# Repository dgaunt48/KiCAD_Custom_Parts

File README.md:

# KiCad Custom Parts

Symbols, Footprints and 3dModels used in my schematics which are not part of the standard KiCad libraries.

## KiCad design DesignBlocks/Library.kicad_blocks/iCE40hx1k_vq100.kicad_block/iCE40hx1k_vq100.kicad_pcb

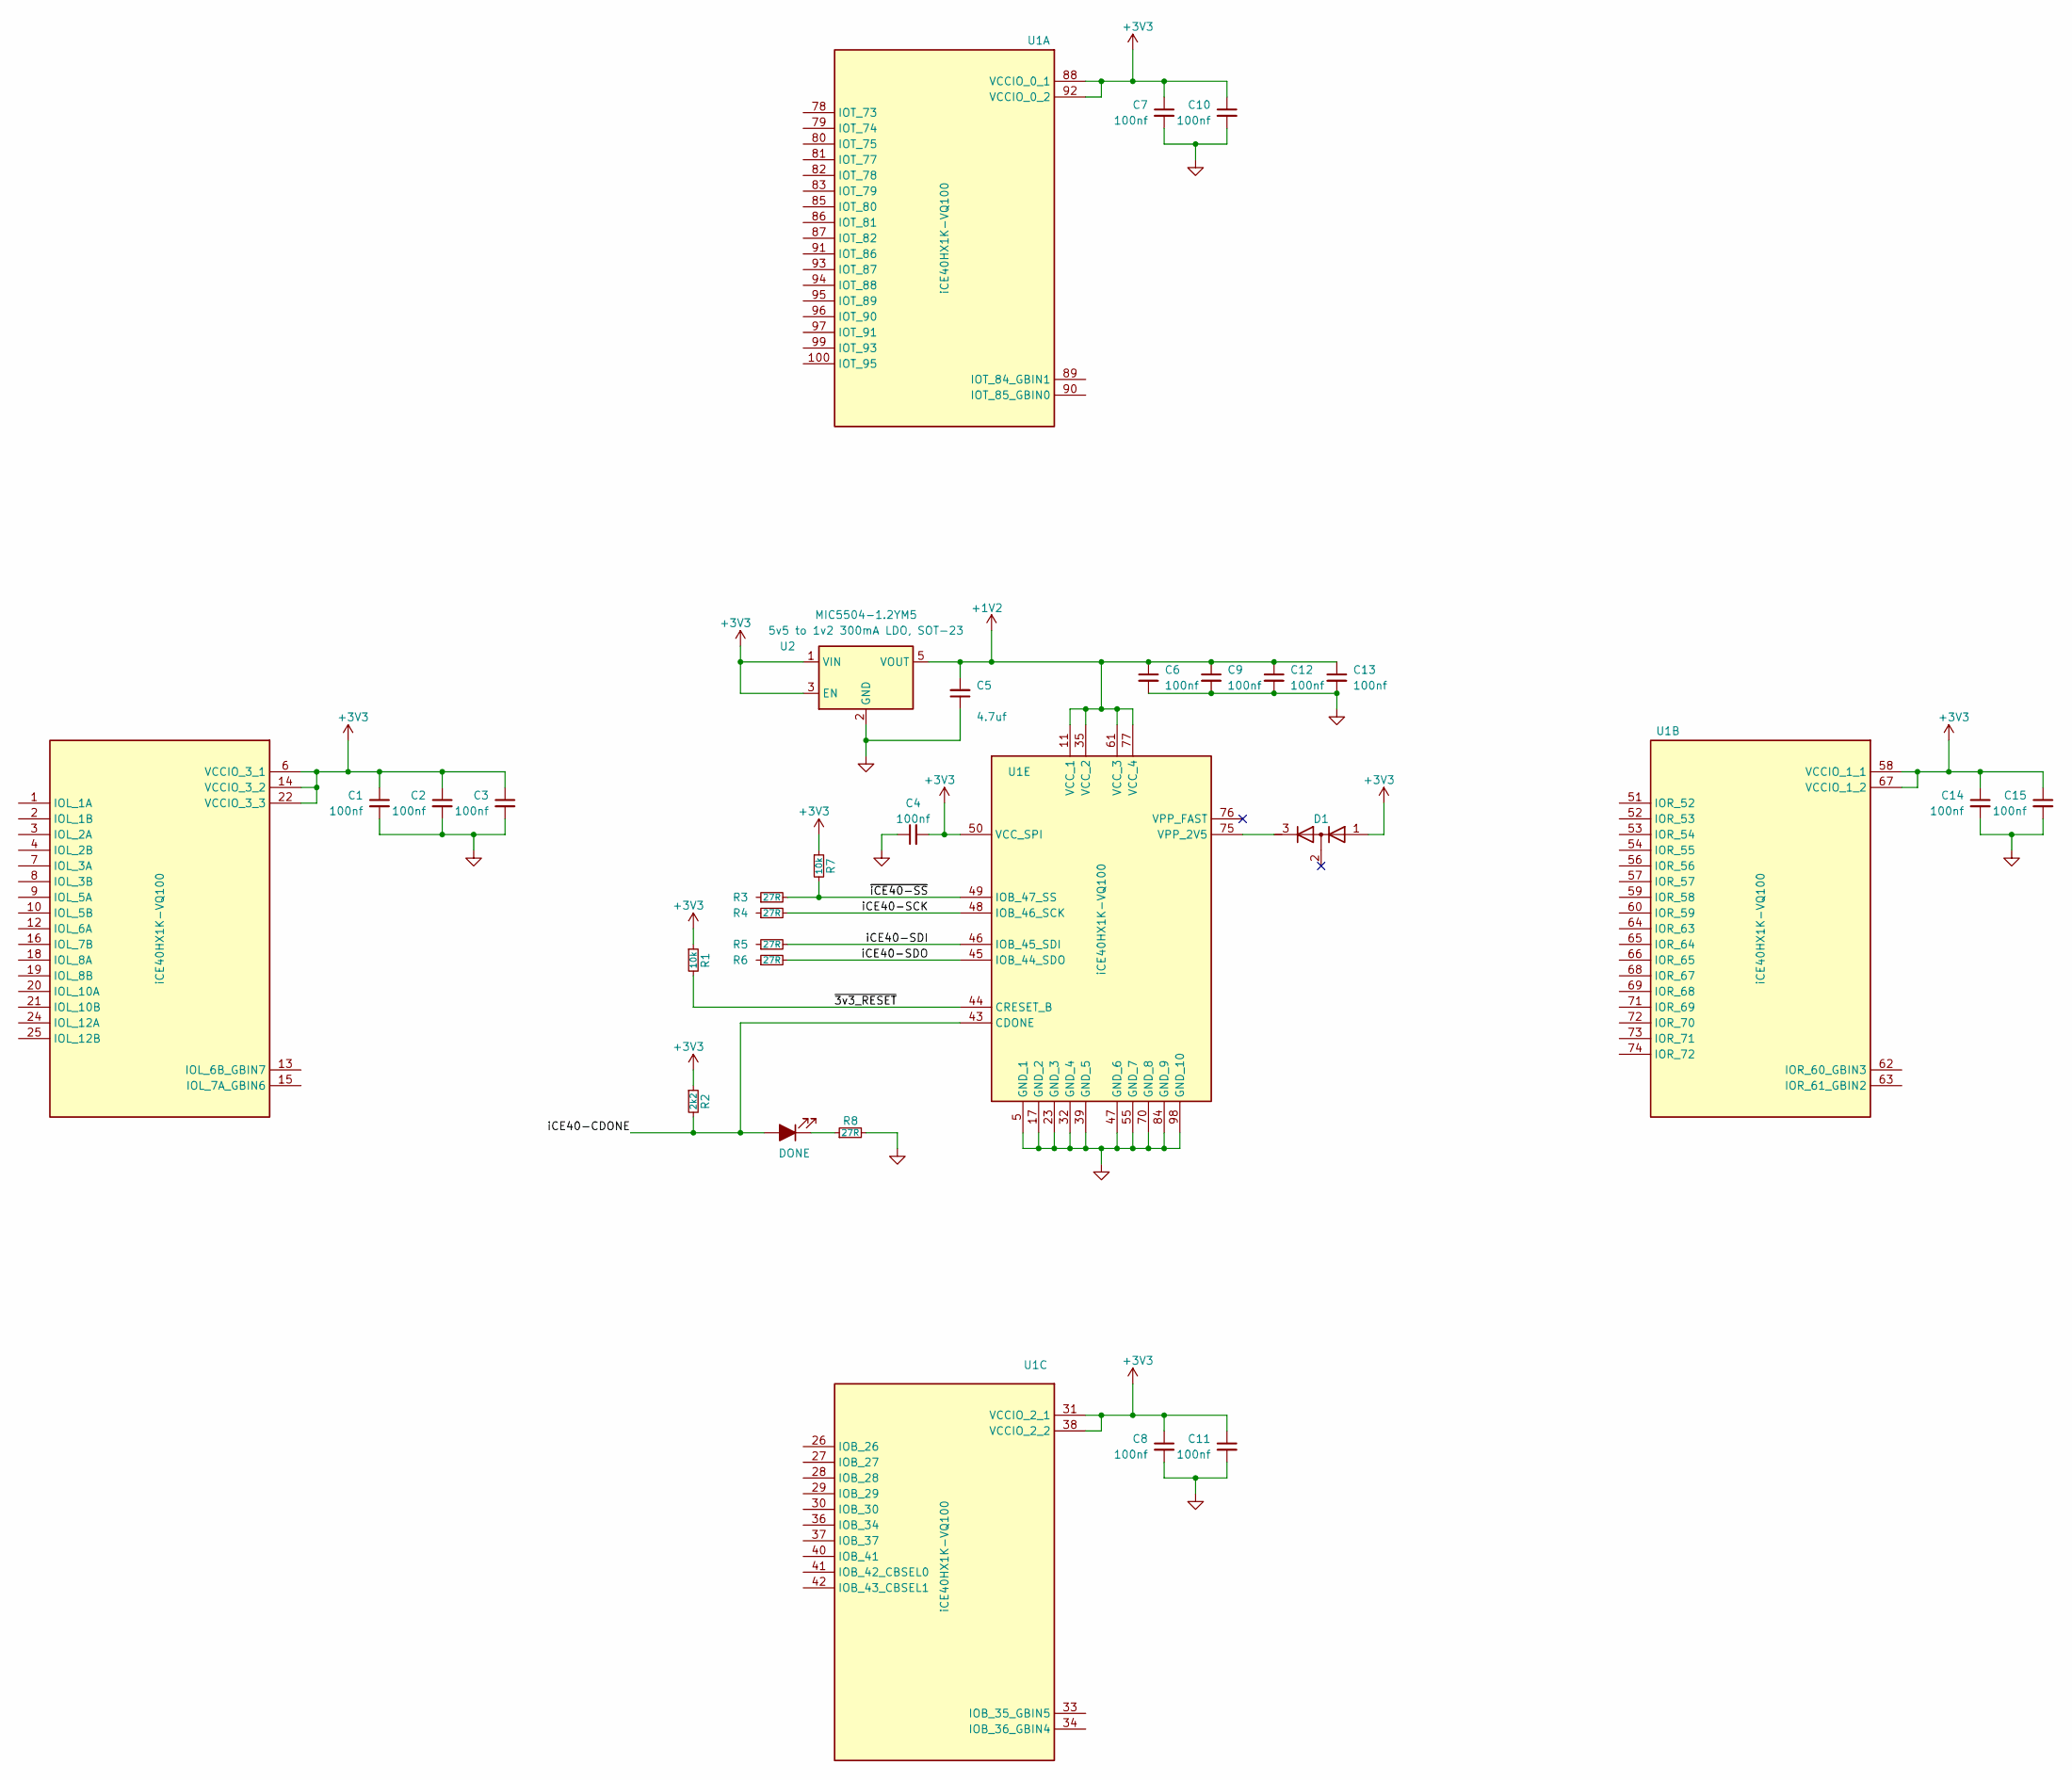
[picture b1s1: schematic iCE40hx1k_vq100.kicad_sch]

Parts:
C1, C2, C3, C4, C6, C7, C8, C9, C10, C11, C12, C13, C14, C15: 100nf; C_0603_1608Metric
C5: 4.7uf; C_0603_1608Metric
CDone1: DONE; LED_0805_2012Metric
D1: D_Dual_Series_ACK; SOT-23
R1, R7: 10k; R_0603_1608Metric
R2: 2k2; R_0603_1608Metric
R3, R4, R5, R6, R8: 27R; R_0603_1608Metric
U1: iCE40HX1K-VQ100; LQFP-100_14x14mm_P0.5mm; Mouser Part Number 842-ICE40HX4K-TQ144
U2: MIC5504-1.2YM5; SOT-23-5; Voltage 1v2

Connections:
+1V2: C5.2, C6.1, C9.1, C12.1, C13.1, U1.11 (VCC_1), U1.35 (VCC_2), U1.61 (VCC_3), U1.77 (VCC_4), U2.5 (VOUT)
+3V3: C1.1, C2.1, C3.1, C4.2, C7.1, C8.1, C10.1, C11.1, C14.1, C15.1, D1.1 (A), R1.1, R2.1, R7.1, U1.6 (VCCIO_3_1), U1.14 (VCCIO_3_2), U1.22 (VCCIO_3_3), U1.31 (VCCIO_2_1), U1.38 (VCCIO_2_2), U1.50 (VCC_SPI), U1.58 (VCCIO_1_1), U1.67 (VCCIO_1_2), U1.88 (VCCIO_0_1), U1.92 (VCCIO_0_2), U2.1 (VIN), U2.3 (EN)
/iCE40-CDONE: CDone1.2 (A), R2.2, U1.43 (CDONE)
/iCE40-SCK: R4.2, U1.48 (IOB_46_SCK)
/iCE40-SDI: R5.2, U1.46 (IOB_45_SDI)
/iCE40-SDO: R6.2, U1.45 (IOB_44_SDO)
/~3v3_RESET: R1.2, U1.44 (CRESET_B)
/~iCE40-SS: R3.2, R7.2, U1.49 (IOB_47_SS)
GND: C1.2, C2.2, C3.2, C4.1, C5.1, C6.2, C7.2, C8.2, C9.2, C10.2, C11.2, C12.2, C13.2, C14.2, C15.2, R8.2, U1.5 (GND_1), U1.17 (GND_2), U1.23 (GND_3), U1.32 (GND_4), U1.39 (GND_5), U1.47 (GND_6), U1.55 (GND_7), U1.70 (GND_8), U1.84 (GND_9), U1.98 (GND_10), U2.2 (GND)
unnamed: CDone1.1 (K), R8.1
unnamed: D1.3 (K), U1.75 (VPP_2V5)

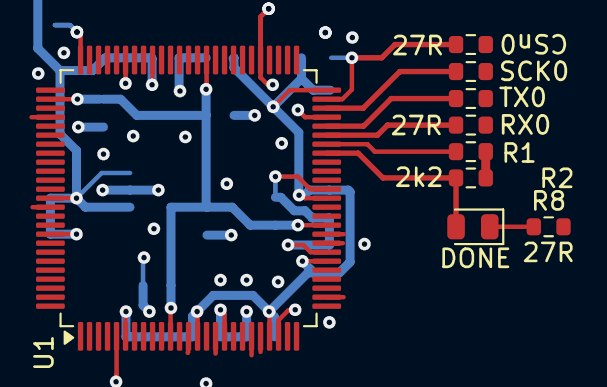
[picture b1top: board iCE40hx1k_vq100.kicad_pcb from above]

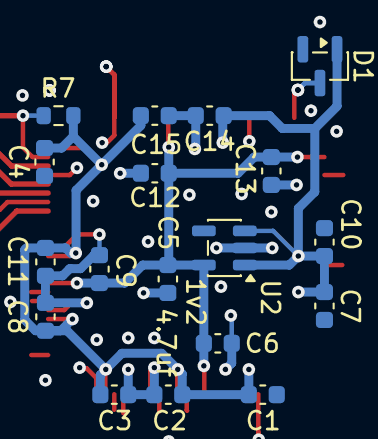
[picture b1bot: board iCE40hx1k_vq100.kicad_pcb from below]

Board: 2 copper layers, 27 parts (18 on the bottom side), 11 nets.

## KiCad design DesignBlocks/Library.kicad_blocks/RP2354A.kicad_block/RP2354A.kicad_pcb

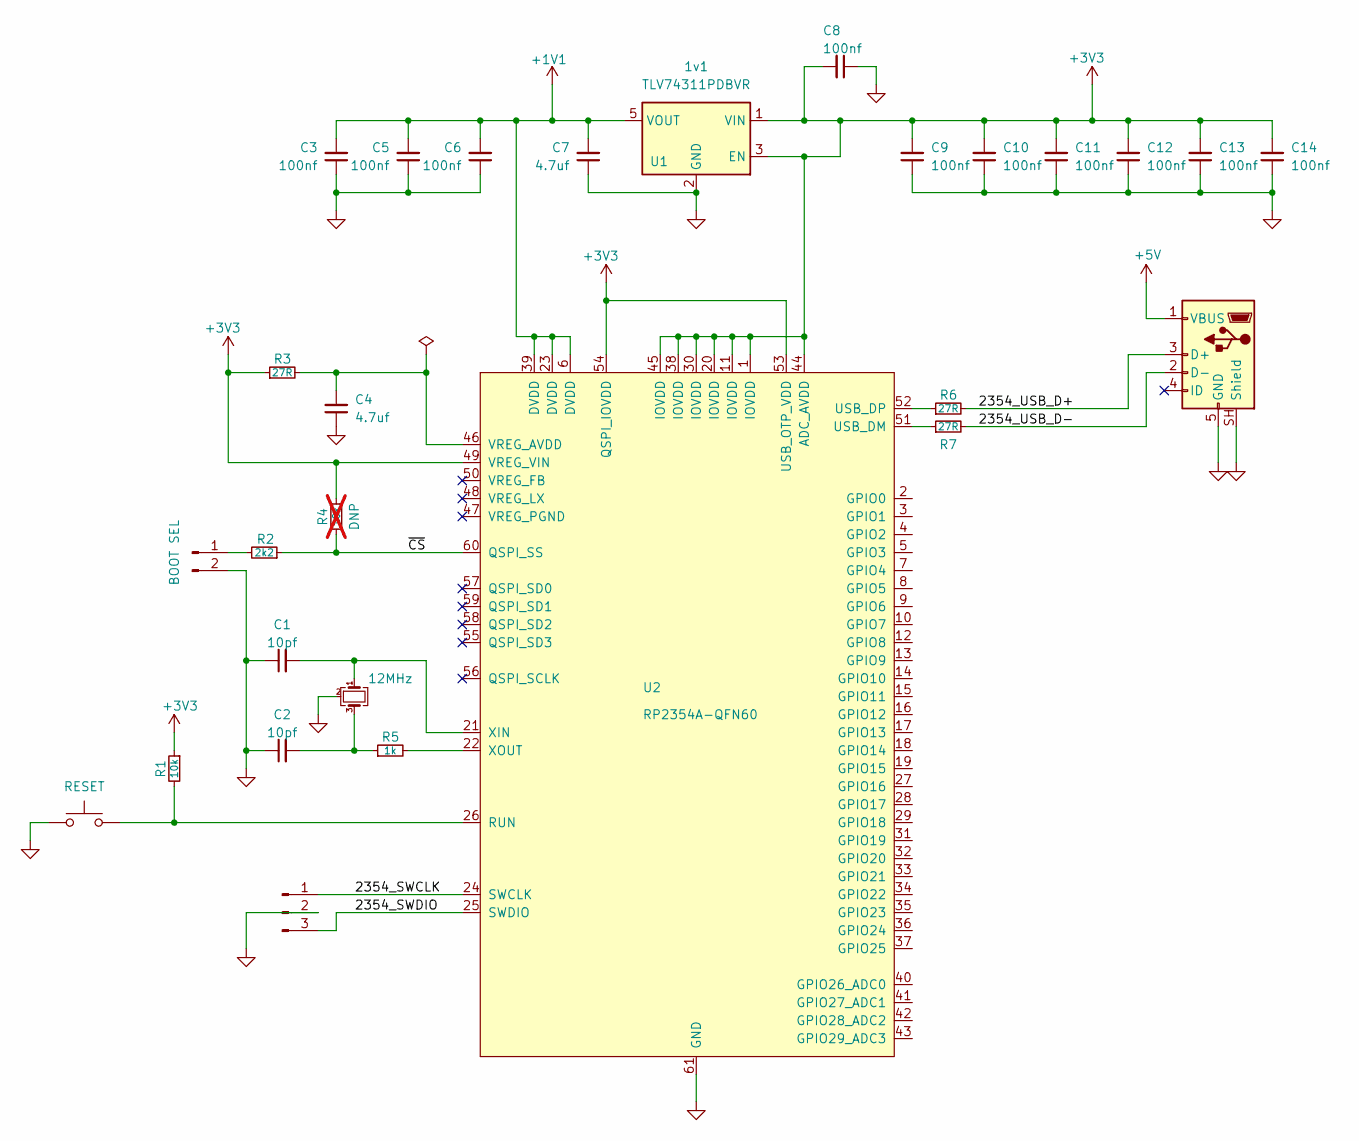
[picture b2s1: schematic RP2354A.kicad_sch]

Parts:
C1, C2: 10pf; C_0603_1608Metric
C3, C5, C6, C8, C9, C10, C11, C12, C13, C14: 100nf; C_0603_1608Metric
C4, C7: 4.7uf; C_0603_1608Metric
J1: SWD; PinHeader_1x03_P2.54mm_Vertical
J2: USB_B_Micro; USB_Micro-B_Amphenol_10103594-0001LF_Horizontal
Je1: BOOT SEL; PinHeader_1x02_P2.54mm_Vertical
R1: 10k; R_0603_1608Metric
R2: 2k2; R_0603_1608Metric
R3, R6, R7: 27R; R_0603_1608Metric
R4: 10k; R_0603_1608Metric; not fitted
R5: 1k; R_0603_1608Metric
S1: RESET; SW_PUSH_6mm_H4.3mm; Mouser Part Number 653-B3F-1052-G
U1: TLV74311PDBVR; SOT-23-5; Voltage 1v1
U2: RP2354A-QFN60; RP2350A_QFN-60_EP_7.75x7.75_Pitch0.4mm
Y1: 12MHz; Crystal_SMD_SeikoEpson_FA238V-4Pin_3.2x2.5mm

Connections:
+1V1: C3.2, C5.2, C6.2, C7.2, U1.5 (VOUT), U2.6 (DVDD), U2.23 (DVDD), U2.39 (DVDD)
+3V3: C8.2, C9.2, C10.2, C11.2, C12.2, C13.2, C14.2, R1.1, R3.1, R4.1, U1.1 (VIN), U1.3 (EN), U2.1 (IOVDD), U2.11 (IOVDD), U2.20 (IOVDD), U2.30 (IOVDD), U2.38 (IOVDD), U2.44 (ADC_AVDD), U2.45 (IOVDD), U2.49 (VREG_VIN), U2.53 (USB_OTP_VDD), U2.54 (QSPI_IOVDD)
+5V: J2.1 (VBUS)
/2354_SWCLK: J1.1, U2.24 (SWCLK)
/2354_SWDIO: J1.3, U2.25 (SWDIO)
/2354_USB_D+: J2.3 (D+), R6.2
/2354_USB_D-: J2.2 (D-), R7.2
/~CS: R2.1, R4.2, U2.60 (QSPI_SS)
GND: C1.1, C2.1, C3.1, C4.1, C5.1, C6.1, C7.1, C8.1, C9.1, C10.1, C11.1, C12.1, C13.1, C14.1, J1.2, J2.5 (GND), J2.SH (Shield), Je1.2, S1.2, U1.2 (GND), U2.61 (GND), Y1.2 (G), Y1.4 (G)
unnamed: C2.2, R5.1, Y1.3
unnamed: Je1.1, R2.2
unnamed: R1.2, S1.1, U2.26 (RUN)
unnamed: R7.1, U2.51 (USB_DM)
unnamed: R6.1, U2.52 (USB_DP)
unnamed: C4.2, R3.2, U2.46 (VREG_AVDD)
unnamed: C1.2, U2.21 (XIN), Y1.1
unnamed: R5.2, U2.22 (XOUT)

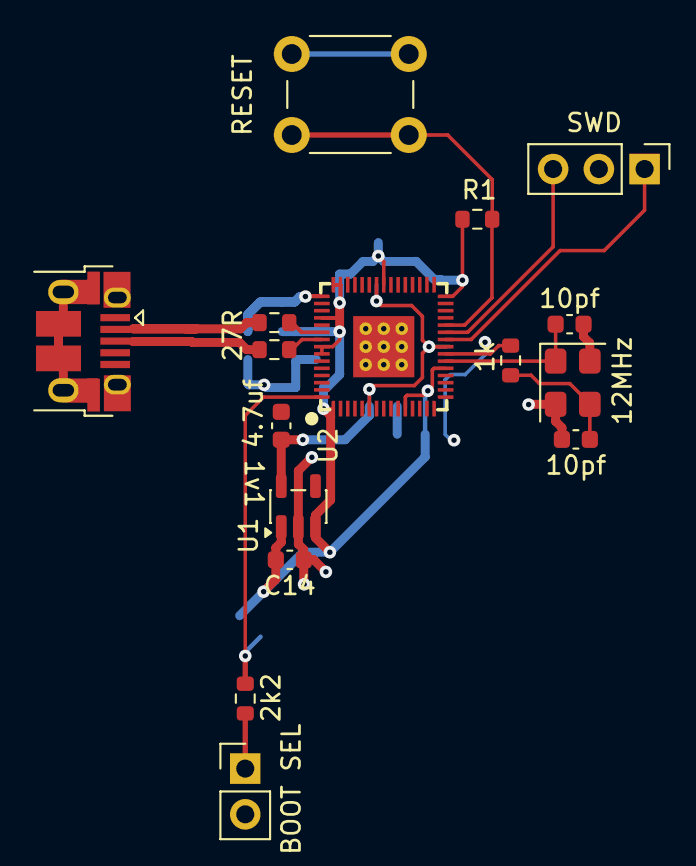
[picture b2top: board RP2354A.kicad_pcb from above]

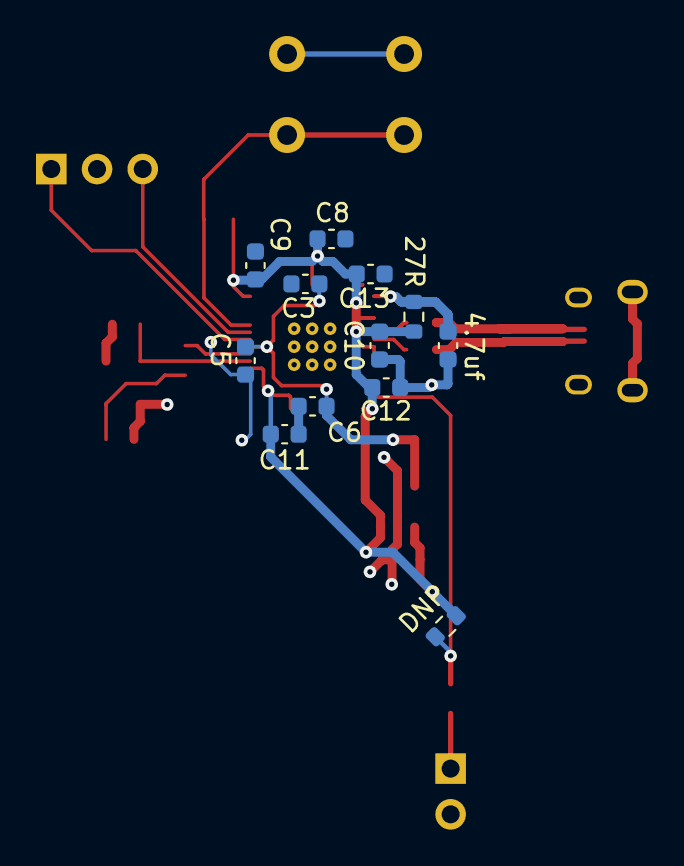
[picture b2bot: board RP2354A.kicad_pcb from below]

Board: 2 copper layers, 28 parts (12 on the bottom side), 16 nets.

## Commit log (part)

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2026-06-20 - Added Some Footprints And Symbols From My Schematics.
